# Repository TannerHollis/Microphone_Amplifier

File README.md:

# Microphone Amplifier

## Introduction
This project features a variable gain amplifier used to control the gain of a simple electret condenser, also known as a microphone. While this board may look very basic, the application uses of this can be *very* involved. 

## Op-Amp
Op-Amps, or Operational Amplifiers, are used everywhere. At its core, it takes an input and scales it by some factor at the output. Yet it's not that easy. There are a lot different configurations one can do with a basic Op-Amp and one must think of the desired use to figure out the configuration to be used. 

### Inverting Amplifier and Changing the Gain
The most basic Op-Amp use is the inverting amplifier ([Inverting Operational Amplifier](https://www.electronics-tutorials.ws/opamp/opamp_2.html)) as shown below.

It is configurable so that the input can be scaled by a simple equation:

    Av = -Rf / Rin

One can control the gain, `Av`, by simply choosing resistors values for both `Rin` and `Rf`. The exact workings behind the Op-Amp are fundamental to closed-loop systems, which I won't cover in this project. Just know that the feedback resistor, `Rf`, is necessary to control the closed-loop gain.

If one wants the change the gain of the Op-Amp, one must swap out the value of the feedback resistor. And this is the problem. **The intended use of this microphone amplifier is to amplify the input signal coming from the electret microphone, and the exact input signal varies wildly from microVolts to milliVolts.** The input signal from the microphone varies with the loudness of speech, music, e.t.c. In the presence of a quiet sound, the input signal will be very small, yet in the presence of a loud sound, the input signal will be very large.

In order to receive an output signal that is properly amplified throughout the entirety of its operation, one would have to change the resistor value constantly in order to maintain proper amplification. For this problem, there exists a component called the potentiometer. A potentiometer has a small knob and one can vary the resistance between a certain value by twisting the knob. Inside of the potentiometer is a small "wiper", which acts as a little needle that interrupts the total resistance proportional to the position relative to one side or another. The actual resistance on one side of the potentiometer is a function of the position of the knob.  Potentiometers exist in many different values, such as 1kOhm, 5kOhm, 50kOhm and 100kOhm. These exist for many different purposes, but for this case a 100kOhm potentiometer was used to provide the following range of gains:
```
Rin = 470
Av_0 = -0 / 470 = 0
Av_100k = -100e3 / 470 = 212.8
```
Theoretically, one could twist the potentiometer to adjust the gain of the amplifier to select the proper amplification. This would quickly become very cumbersome, therefore a solution is needed.

## Digital Potentiometer
There is a component called a digital potentiometer which is essentially a potentiometer that is configurable via digital communication. In our problem, we need to vary the feedback resistance very quickly, nearly instantaneously based on the received output signal.

The digital potentiometer used in this amplifier is an [MCP4151](http://ww1.microchip.com/downloads/en/devicedoc/22060b.pdf), which has 257 steps with the full range of 100kOhms. This means, each step is equal to 389.1Ohms.

    Av_n = -389.1 / 470 * n = -0.828 * n

This level of granularity enables us to control the gain with a fine amount of control. In order to communicate with the MCP4151, we must refer to the datasheet. Skipping all of the basics of SPI communication, we may refer to the datasheet SPI command example.

As seen above, the command contains three components, the memory address, the command and the data. All of this is compacted into a 16-bit command. While it would be nice to read data from the MCP4151, in this project we are only concerned with the write function and we will assume that the MCP4151 will function properly and the wiper is set correctly.

The following is the register contents of the MCP4151, which shows the internal registers and data format expected via SPI communication.

For example, if we wanted to set the resistance to 50kOhms, we would first have to find the step at which this value occurs.

    Ra = (389.1 * n) # We want this value
    Rb = (389.1 * (257 - n))
    50e3 = (389.1 * n) = 50e3 / 389.1 = n
    n = 128.5 ~= 128

Now that we've found the wiper value that we want to send to the MCP4151, we need to compile the full instruction.

    CMD = 0h 	//Write Value
    ADDR = 00h	//Wiper 0
    DATA = 128 = 81h
    
    //Combine the data
    uint8_t data[2];
    data[0] = ADDR << 4;	//Shift the address to align it properly
    data[0] |= CMD << 2;	//Shift the command to align it properly
    data[1] = DATA;
If everything is setup properly, the wiper should attain the value of 128 and the resistance on each side of the wiper should be approximately 50kOhms. Since this project is only considerate of one side of the digital potentiometer, the other side, Rb, is ignored and left unconnected.

## Algorithm
Since we are going to control the digital potentiometer rapidly, we must develop an algorithm to control the level of gain we need. When stepping into algorithms, the options we have can be limitless. While it would be ideal to have a complex algorithm that would detect RMS values, and calculate the gain from the inverse RMS value. For the sake of my sanity, I am going to keep it simple, stupid (KISS).

The following is the algorithm steps:
 1. Fill ADC data buffer through DMA.
 2. Once DMA buffer is half-full, trigger software event and write gain value to MCP 4151.
 3. Parse data for max, `max`, and min,  `min`.
 4. Determine which is larger, using `level = max(max - 2048, 1.65 - 2048)`.
 5. Determine the expected output signal level `level_e`.
 6. Perform calculation to determine new gain level:
	 a. `Av_n+1 = Av_n * (level_e / level)`
7. Goto Step 1.

Steps 1 through 2 prepare data to be worked with. Once the buffer is half full, the previously written half is ready to manipulate without values becoming overwritten. The reason we write the wiper value here is to assure all the data in the next buffer will have the same level of gain.

Step 3 will simply iterate through the entire buffer recording the minimum and maximum values, stored in a 12-bit value from the ADC.

Step 4 then determines the maximum level with respect to the 1.65V offset, value 2048. This accounts for negative and positive swings throughout the buffer.

Step 5 is not really a step, essentially is is the value that the user wants to receive the signal at. For instance, if the user wants the value to be 1.5V pk-pk, `V_e`, the `level_e` should be set accordingly to `level_e = V_e * 4096 / (3.3 * 2) = 1.5 * 4096 / (3.3 * 2) = 930.9 ~= 930`.

Step 6 simply calculates the new gain using the old gain value.

It might seem odd that we don't set the MCP4151 wiper right away, but we are dealing with old data and the processing time associated with the algorithm adds an additional delay. If we were to set the new gain value after we calculate it, we risk changing the gain value some number of values into the next buffer. Throwing off the received values. Settings the gain once we enter the algorithm is fundamental to ensuring that the entire buffer we are processing contains values that are scaled by the same gain value.

## Schematic

The microphone amplifier is simplified with a decoupling capacitor which fundamentally only allows AC voltage to pass through to the amplifier. The voltage offset is set by a resistor divider which is fed into a voltage follower, which outputs a VCC/2 output. The voltage follower essentially has a high impedance input and a low impedance output, eliminating any offset due to using a voltage divider circuit directly into the non-inverting Op-Amp input (this may seem abstract but a low impedance output is highly desirable in analog circuits. Inversely, a high impedance input is always desired).

The MCP4151 is as easy as following the datasheet for pins and connections.

The rest are headers, one (J1) for an input header and the other (J2) for a RC filter selection.

### RC Filter
The output of the amplifier is a low-pass filter, which filters out high frequency signals. The purpose of this filter is to reduce the amount of noise that may exist on the circuit due to noise or poor input voltages. The RC filter is as simple as a resistor and capacitor divider, where the capacitor absorbs the higher frequency components. The design of an RC filter is as easy as selecting a cutoff frequency, where the signal output will be exactly half of the input frequency (attenuation). The governing equation for an RC filter is defined as:

    f_c = 1 / (2 * pi * R * C)

In this design, a header jumper may be moved to either select 22kHz or 1.2kHz as a cutoff frequency, otherwise the removal of the jumper will bypass this filter and there is no low-pass filter applied.

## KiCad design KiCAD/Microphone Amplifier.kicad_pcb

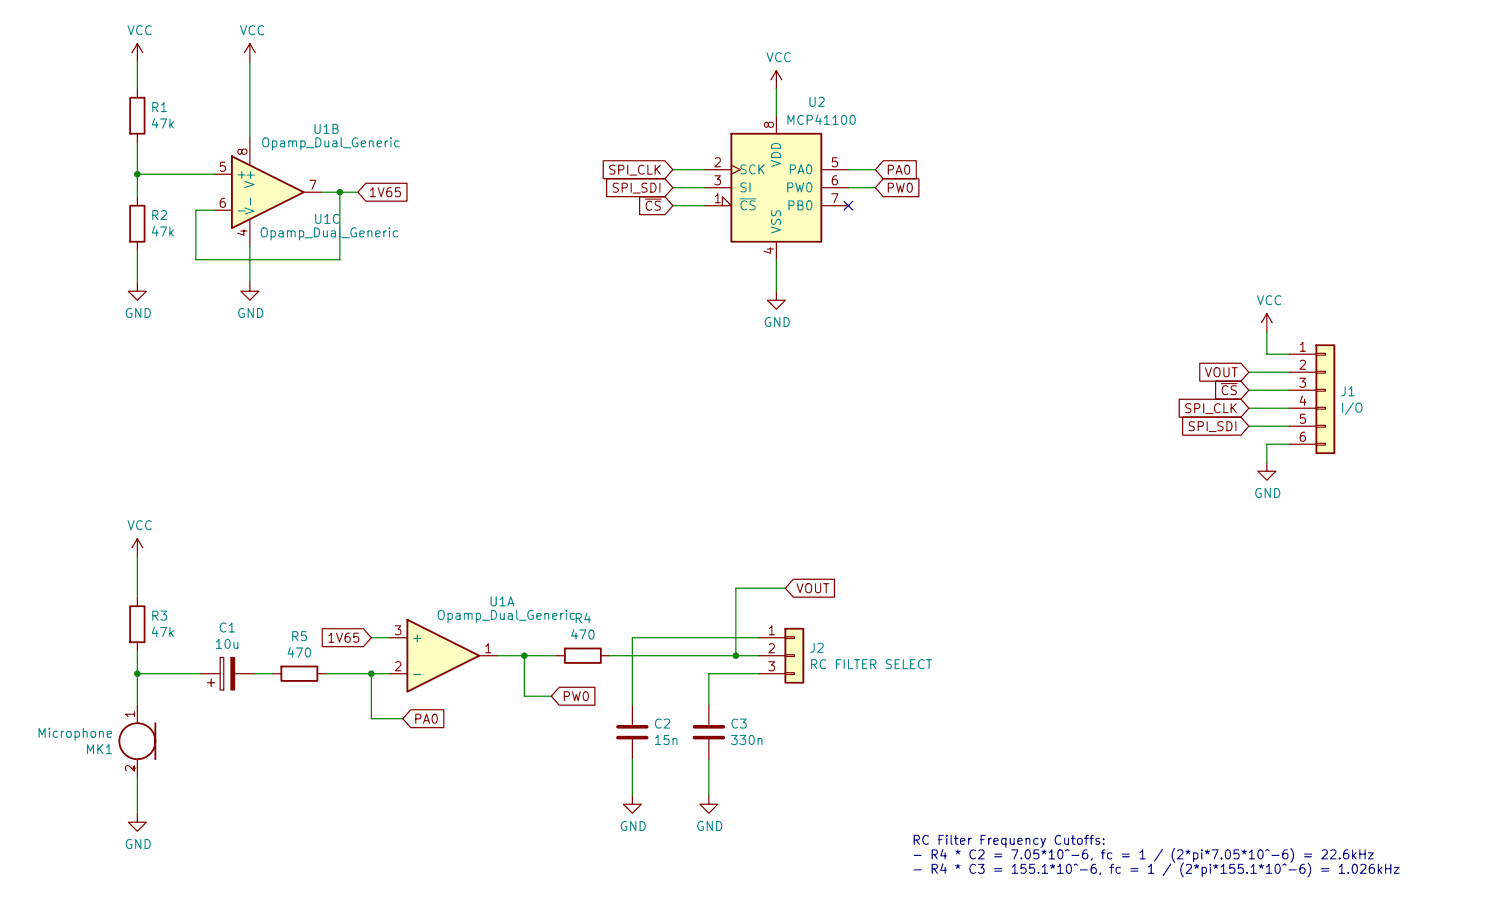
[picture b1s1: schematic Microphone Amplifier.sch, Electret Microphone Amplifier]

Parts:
C1: 10u; CP_Radial_D5.0mm_P2.00mm
C2: 15n; C_Rect_L7.2mm_W3.5mm_P5.00mm_FKS2_FKP2_MKS2_MKP2
C3: 330n; C_Rect_L7.2mm_W3.5mm_P5.00mm_FKS2_FKP2_MKS2_MKP2
J1: I/O; PinHeader_1x06_P2.54mm_Vertical
J2: RC FILTER SELECT; PinHeader_1x03_P2.54mm_Vertical
MK1: Microphone; MIC_CMA-4544PF-W
R1, R2, R3: 47k; R_Axial_DIN0207_L6.3mm_D2.5mm_P7.62mm_Horizontal
R4, R5: 470; R_Axial_DIN0207_L6.3mm_D2.5mm_P7.62mm_Horizontal
U1: Opamp_Dual_Generic; DIP-8_W7.62mm
U2: MCP41100; DIP-8_W7.62mm

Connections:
1V65: U1.3 (+), U1.6 (-), U1.7
GND: C2.2, C3.2, J1.6, MK1.2 (+), R2.2, U1.4 (V-), U2.4 (VSS)
unnamed: C1.1, MK1.1 (-), R3.2
unnamed: C1.2, R5.2
unnamed: C2.1, J2.1
unnamed: C3.1, J2.3
unnamed: R1.2, R2.1, U1.5 (+)
PA0: R5.1, U1.2 (-), U2.5 (PA0)
PW0: R4.2, U1.1, U2.6 (PW0)
SPI_CLK: J1.4, U2.2 (SCK)
SPI_SDI: J1.5, U2.3 (SI)
VCC: J1.1, R1.1, R3.1, U1.8 (V+), U2.8 (VDD)
VOUT: J1.2, J2.2, R4.1
~CS~: J1.3, U2.1 (~CS)

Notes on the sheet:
RC Filter Frequency Cutoffs: - R4 * C2 = 7.05*10^-6, fc = 1 / (2*pi*7.05*10^-6) = 22.6kHz - R4 * C3 = 155.1*10^-6, fc = 1 / (2*pi*155.1*10^-6) = 1.026kHz

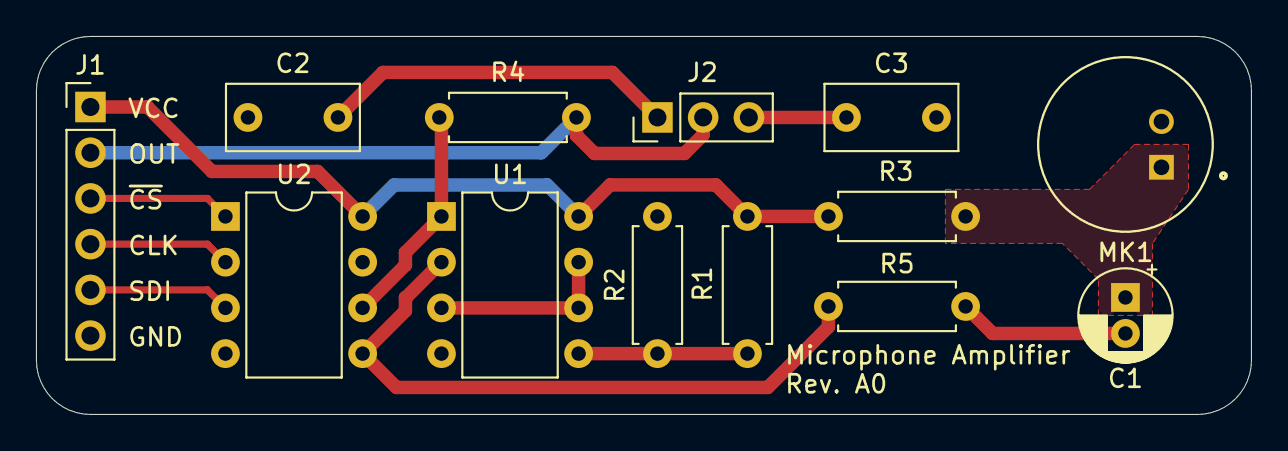
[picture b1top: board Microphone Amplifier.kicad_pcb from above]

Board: 2 copper layers, 67.5 x 21.0 mm, 13 parts (0 on the bottom side), 14 nets.

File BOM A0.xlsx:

Bill of Materials
Microphone Amplifier |  |  |  | Started: March 25th, 2022 Finished:
 |  |  |  | Total Components | 10 |  | Total Cost | 13.5
 |  |  |  | Boards | 5
Component | Reference(s) | Value | JLCPCB Code | Digikey Code | Quantity | Total Quantity | Cost Per | Subtotal
1 | C1 | 10u |  | 732-8593-1-ND | 1 | 5 | 0.1 | 0.5
2 | C2 | 15n |  | 399-6035-ND | 1 | 5 | 0.23 | 1.1500000000000001
3 | C3 | 330n |  | 399-5906-ND | 1 | 5 | 0.33 | 1.6500000000000001
4 | J1 | I/O |  |  | 0 | 0 |  | 0
5 | J2 | RC FILTER SELECT |  |  | 0 | 0 |  | 0
6 | MK1 | Microphone |  |  | 0 | 0 |  | 0
7 | R1, R2, R3 | 47k |  | 56-SFR2500004702FR500CT-ND | 3 | 15 | 0.13 | 1.9500000000000002
8 | R4, R5 | 470 |  | 56-SFR2500004700FR500CT-ND | 1 | 5 | 0.13 | 0.65
9 | U1 | AP358 |  | AP358NL-UDI-ND | 1 | 5 | 0.24 | 1.2
10 | U2 | MCP4151-100k |  | MCP4151-104E/P-ND | 1 | 5 | 1.18 | 5.8999999999999995
 |  | Header Jumper |  | S9000-ND | 1 | 5 | 0.1 | 0.5

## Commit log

2022-03-26 A0
    First Revision A0, is up
2022-03-26 A0_00
    Fixed README
2022-03-28 A0_01
    Added Datasheets
2022-03-28 A0_02
    Fixed Op-Amp Drawing
